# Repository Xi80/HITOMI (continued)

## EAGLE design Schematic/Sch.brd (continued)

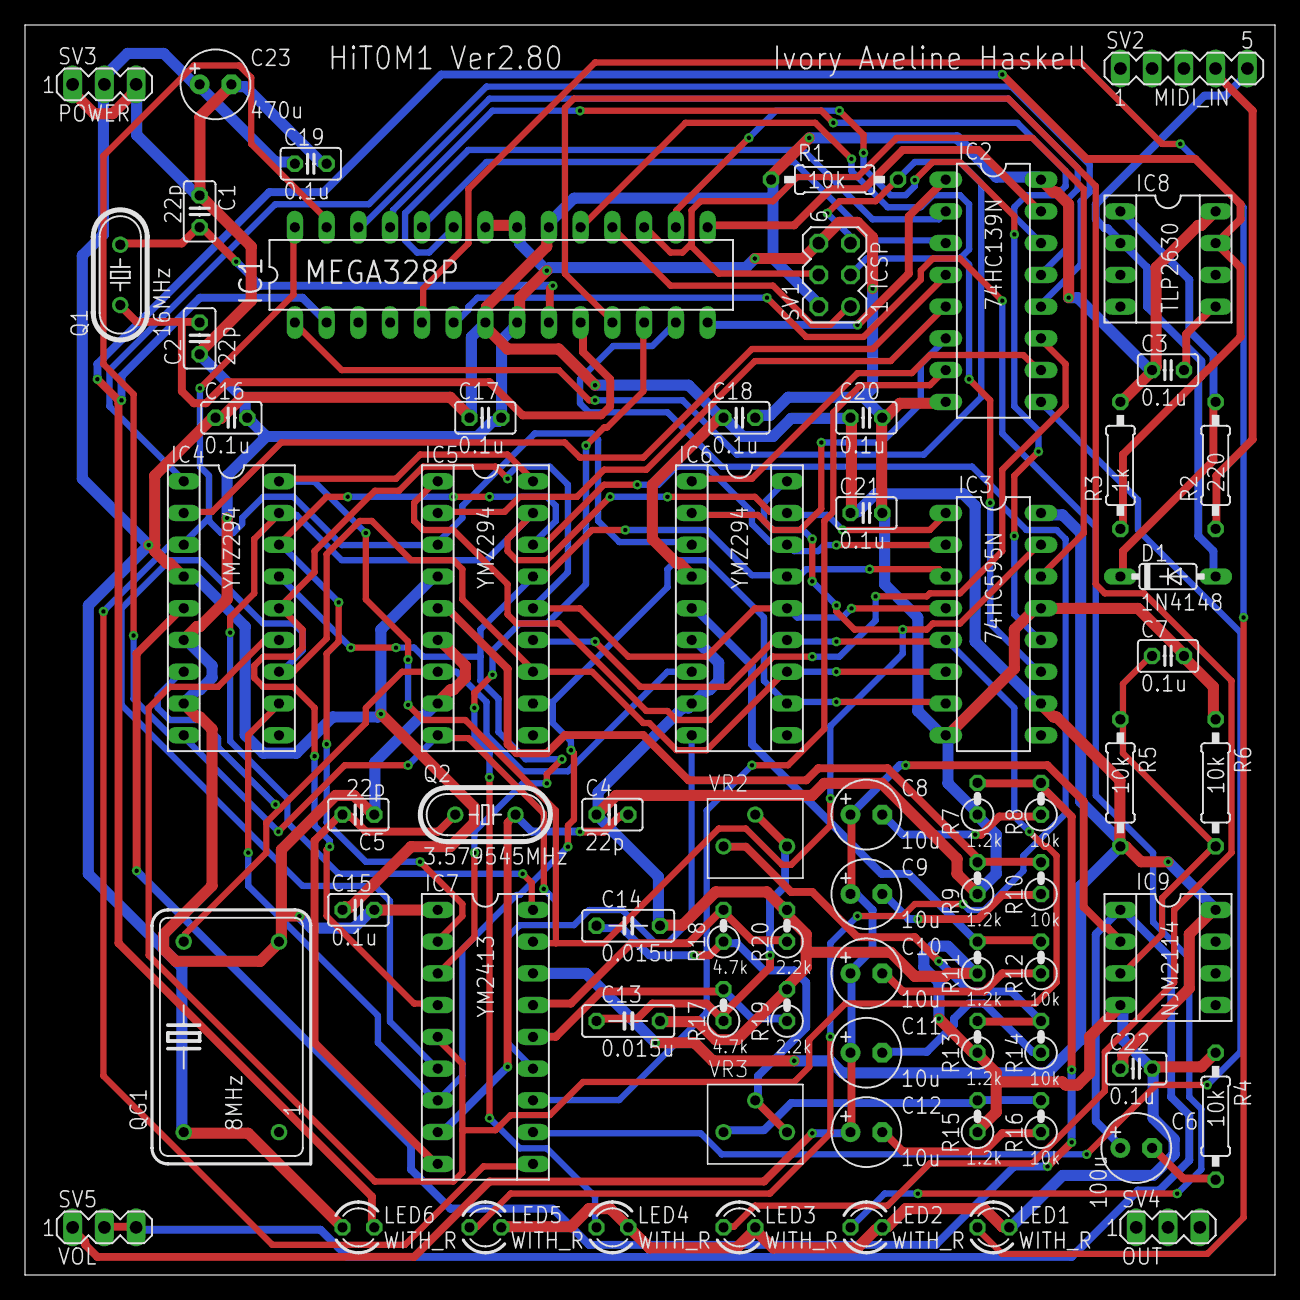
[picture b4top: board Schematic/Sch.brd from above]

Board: 2 copper layers, 100.0 x 100.0 mm, 69 parts (0 on the bottom side), 64 nets.

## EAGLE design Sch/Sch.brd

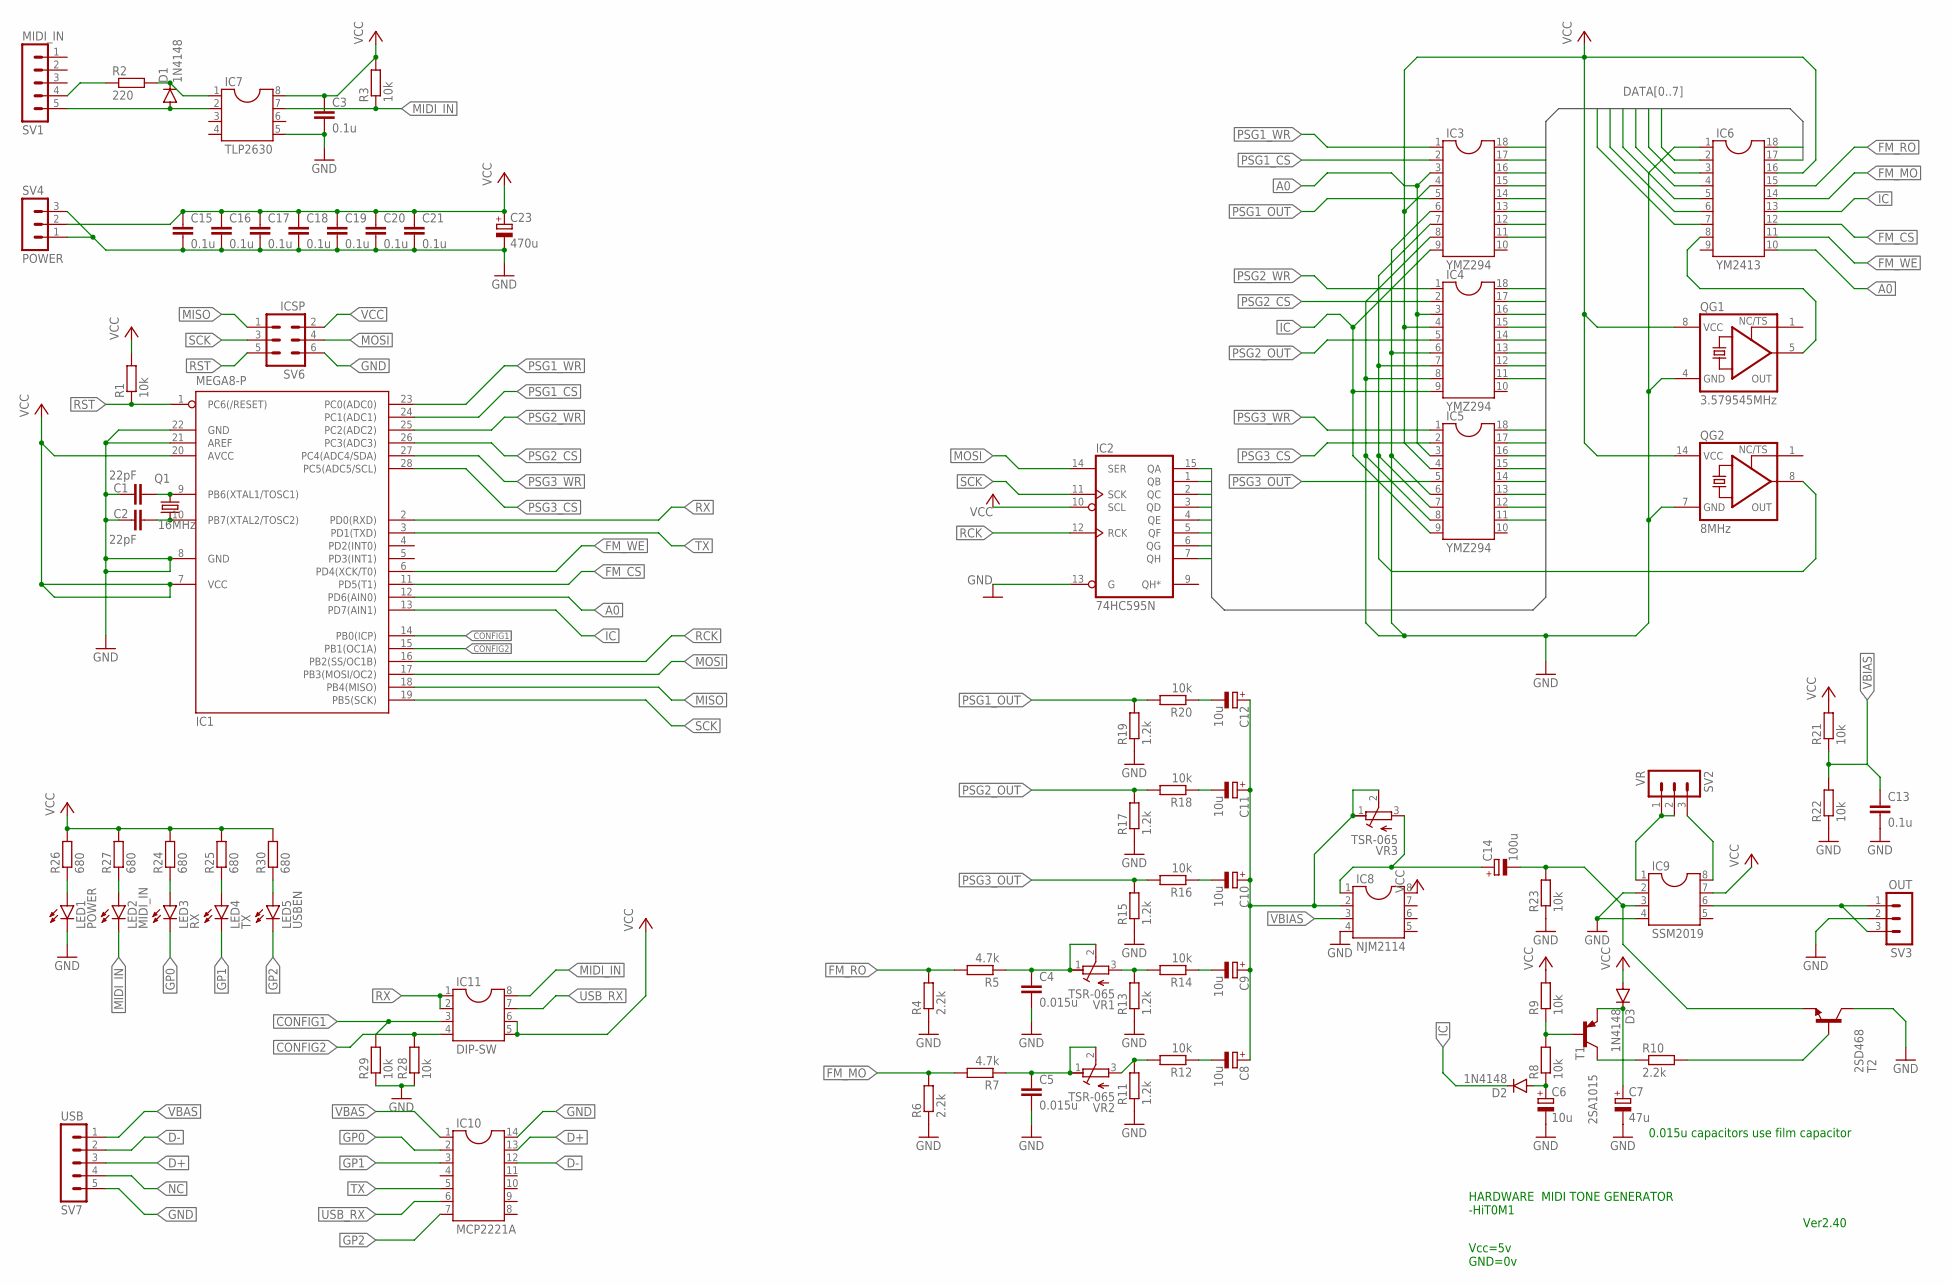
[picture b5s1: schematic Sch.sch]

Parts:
C1, C2: 22pF; C050-025X075
C3, C13, C15, C16, C17, C18, C19, C20, C21: 0.1u; C025-030X050
C4, C5: 0.015u; C050-025X075
C6, C8, C9, C10, C11, C12: 10u; E2,5-5
C7: 47u; E2,5-5
C14: 100u; E2,5-5
C23: 470u; E2,5-5
D1, D2, D3: 1N4148; DO35-7
IC1: MEGA8-P; DIL28-3
IC2: 74HC595N; DIL16
IC3, IC4, IC5: YMZ294; SOCKET-18
IC6: YM2413; SOCKET-18
IC7: TLP2630; SOCKET-08
IC8: NJM2114; SOCKET-08
IC9: SSM2019; SOCKET-08
IC10: MCP2221A; SOCKET-14
IC11: DIP-SW; SOCKET-08
LED1: POWER; LED3MM
LED2: MIDI_IN; LED3MM
LED3: RX; LED3MM
LED4: TX; LED3MM
LED5: USBEN; LED3MM
Q1: 16MHz; HC49/S
QG1: 3.579545MHz; DIL08S
QG2: 8MHz; DIL14S
R1, R3, R8, R9, R12, R14, R16, R18, R20, R21, R22, R23, R28, R29: 10k; 0207/2V
R2: 220; 0207/2V
R4, R6, R10: 2.2k; 0207/2V
R5, R7: 4.7k; 0207/2V
R11, R13, R15, R17, R19: 1.2k; 0207/2V
R24, R25, R26, R27, R30: 680; 0207/2V
SV1: MIDI_IN; MA05-1
SV2: VR; MA03-1
SV3: OUT; MA03-1
SV4: POWER; MA03-1
SV6: ICSP; MA03-2
SV7: USB; MA05-1
T1: 2SA1015; TO92
T2: 2SD468; TO92
VR1, VR2, VR3: TSR-065

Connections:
A0: IC1.12 (PD6(AIN0)), IC3.3, IC4.3, IC5.3, IC6.10
CONFIG1: IC1.14 (PB0(ICP)), IC11.3, R29.2
CONFIG2: IC1.15 (PB1(OC1A)), IC11.4, R28.2
D+: IC10.13, SV7.3
D-: IC10.12, SV7.2
DATA0: IC2.15 (QA), IC3.18, IC4.18, IC5.18, IC6.17
DATA1: IC2.1 (QB), IC3.17, IC4.17, IC5.17, IC6.18
DATA2: IC2.2 (QC), IC3.16, IC4.16, IC5.16, IC6.2
DATA3: IC2.3 (QD), IC3.15, IC4.15, IC5.15, IC6.3
DATA4: IC2.4 (QE), IC3.14, IC4.14, IC5.14, IC6.4
DATA5: IC2.5 (QF), IC3.13, IC4.13, IC5.13, IC6.5
DATA6: IC2.6 (QG), IC3.12, IC4.12, IC5.12, IC6.6
DATA7: IC2.7 (QH), IC3.11, IC4.11, IC5.11, IC6.7
FM_CS: IC1.11 (PD5(T1)), IC6.12
FM_MO: IC6.14, R6.2, R7.2
FM_RO: IC6.15, R4.2, R5.2
FM_WE: IC1.6 (PD4(XCK/T0)), IC6.11
GND: C1.2, C2.2, C3.2, C4.2, C5.2, C6.-, C7.-, C13.2, C15.2, C16.2, C17.2, C18.2, C19.2, C20.2, C21.2, C23.-, IC1.8 (GND), IC1.21 (AREF), IC1.22 (GND), IC2.8 (GND), IC2.13 (G), IC3.6, IC3.8, IC4.6, IC4.8, IC5.6, IC5.8, IC6.1, IC7.5, IC8.4, IC9.2, IC9.4, IC10.14, LED1.K (C), QG1.4 (GND), QG2.7 (GND), R4.1, R6.1, R11.1, R13.1, R15.1, R17.1, R19.1, R22.1, R23.1, R28.1, R29.1, SV3.2, SV4.1, SV4.3, SV6.6, SV7.5, T2.3 (C)
GP0: IC10.2, LED3.K (C)
GP1: IC10.3, LED4.K (C)
GP2: IC10.7, LED5.K (C)
IC: D2.C, IC1.13 (PD7(AIN1)), IC3.9, IC4.9, IC5.9, IC6.13
MIDI_IN: IC7.7, IC11.8, LED2.K (C), R3.1
MISO: IC1.18 (PB4(MISO)), SV6.1
MOSI: IC1.17 (PB3(MOSI/OC2)), IC2.14 (SER), SV6.4
unnamed: R2.1, SV1.4
unnamed: D1.A, IC7.2, SV1.5
unnamed: C1.1, IC1.9 (PB6(XTAL1/TOSC1)), Q1.2
unnamed: C2.1, IC1.10 (PB7(XTAL2/TOSC2)), Q1.1
unnamed: D1.C, IC7.1, R2.2
unnamed: IC3.7, IC4.7, IC5.7, QG2.8 (OUT)
unnamed: C6.+, D2.A, R8.1
unnamed: C4.1, R5.1, VR1.1 (A), VR1.2 (S)
unnamed: IC6.8, QG1.5 (OUT)
unnamed: C8.+, C9.+, C10.+, C11.+, C12.+, IC8.2, VR3.1 (A), VR3.2 (S)
unnamed: C5.1, R7.1, VR2.1 (A), VR2.2 (S)
unnamed: LED3.A, R24.1
unnamed: R8.2, R9.1, T1.2 (B)
unnamed: C7.+, D3.C, T1.1 (E)
unnamed: R10.1, T1.3 (C)
unnamed: R10.2, T2.2 (B)
unnamed: C14.-, IC9.3, R23.2, T2.1 (E)
unnamed: R11.2, R12.2, VR2.3 (E)
unnamed: C8.-, R12.1
unnamed: R13.2, R14.2, VR1.3 (E)
unnamed: C9.-, R14.1
unnamed: LED4.A, R25.1
unnamed: C10.-, R16.1
unnamed: LED5.A, R30.1
unnamed: C11.-, R18.1
unnamed: LED1.A, R26.1
unnamed: C12.-, R20.1
unnamed: C14.+, IC8.1, VR3.3 (E)
unnamed: IC9.1, SV2.1, SV2.2
unnamed: IC9.8, SV2.3
unnamed: LED2.A, R27.1
unnamed: IC9.6, SV3.1, SV3.3
NC: SV7.4
PSG1_CS: IC1.24 (PC1(ADC1)), IC3.2
PSG1_OUT: IC3.5, R19.2, R20.2
PSG1_WR: IC1.23 (PC0(ADC0)), IC3.1
PSG2_CS: IC1.26 (PC3(ADC3)), IC4.2
PSG2_OUT: IC4.5, R17.2, R18.2
PSG2_WR: IC1.25 (PC2(ADC2)), IC4.1
PSG3_CS: IC1.28 (PC5(ADC5/SCL)), IC5.2
PSG3_OUT: IC5.5, R15.2, R16.2
PSG3_WR: IC1.27 (PC4(ADC4/SDA)), IC5.1
RCK: IC1.16 (PB2(SS/OC1B)), IC2.12 (RCK)
RST: IC1.1 (PC6(/RESET)), R1.1, SV6.5
RX: IC1.2 (PD0(RXD)), IC11.1, IC11.2
SCK: IC1.19 (PB5(SCK)), IC2.11 (SCK), SV6.3
TX: IC1.3 (PD1(TXD)), IC10.5
USB_RX: IC10.6, IC11.7
VBAS: IC10.1, SV7.1
VBIAS: C13.1, IC8.3, R21.1, R22.2
VCC: C3.1, C15.1, C16.1, C17.1, C18.1, C19.1, C20.1, C21.1, C23.+, D3.A, IC1.7 (VCC), IC1.20 (AVCC), IC2.10 (SCL), IC2.16 (VCC), IC3.4, IC4.4, IC5.4, IC6.16, IC7.8, IC8.8, IC9.7, IC11.5, IC11.6, QG1.8 (VCC), QG2.14 (VCC), R1.2, R3.2, R9.2, R21.2, R24.2, R25.2, R26.2, R27.2, R30.2, SV4.2, SV6.2

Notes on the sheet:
HARDWARE MIDI TONE GENERATOR -HiT0M1
Ver2.40
Vcc=5v GND=0v
0.015u capacitors use film capacitor

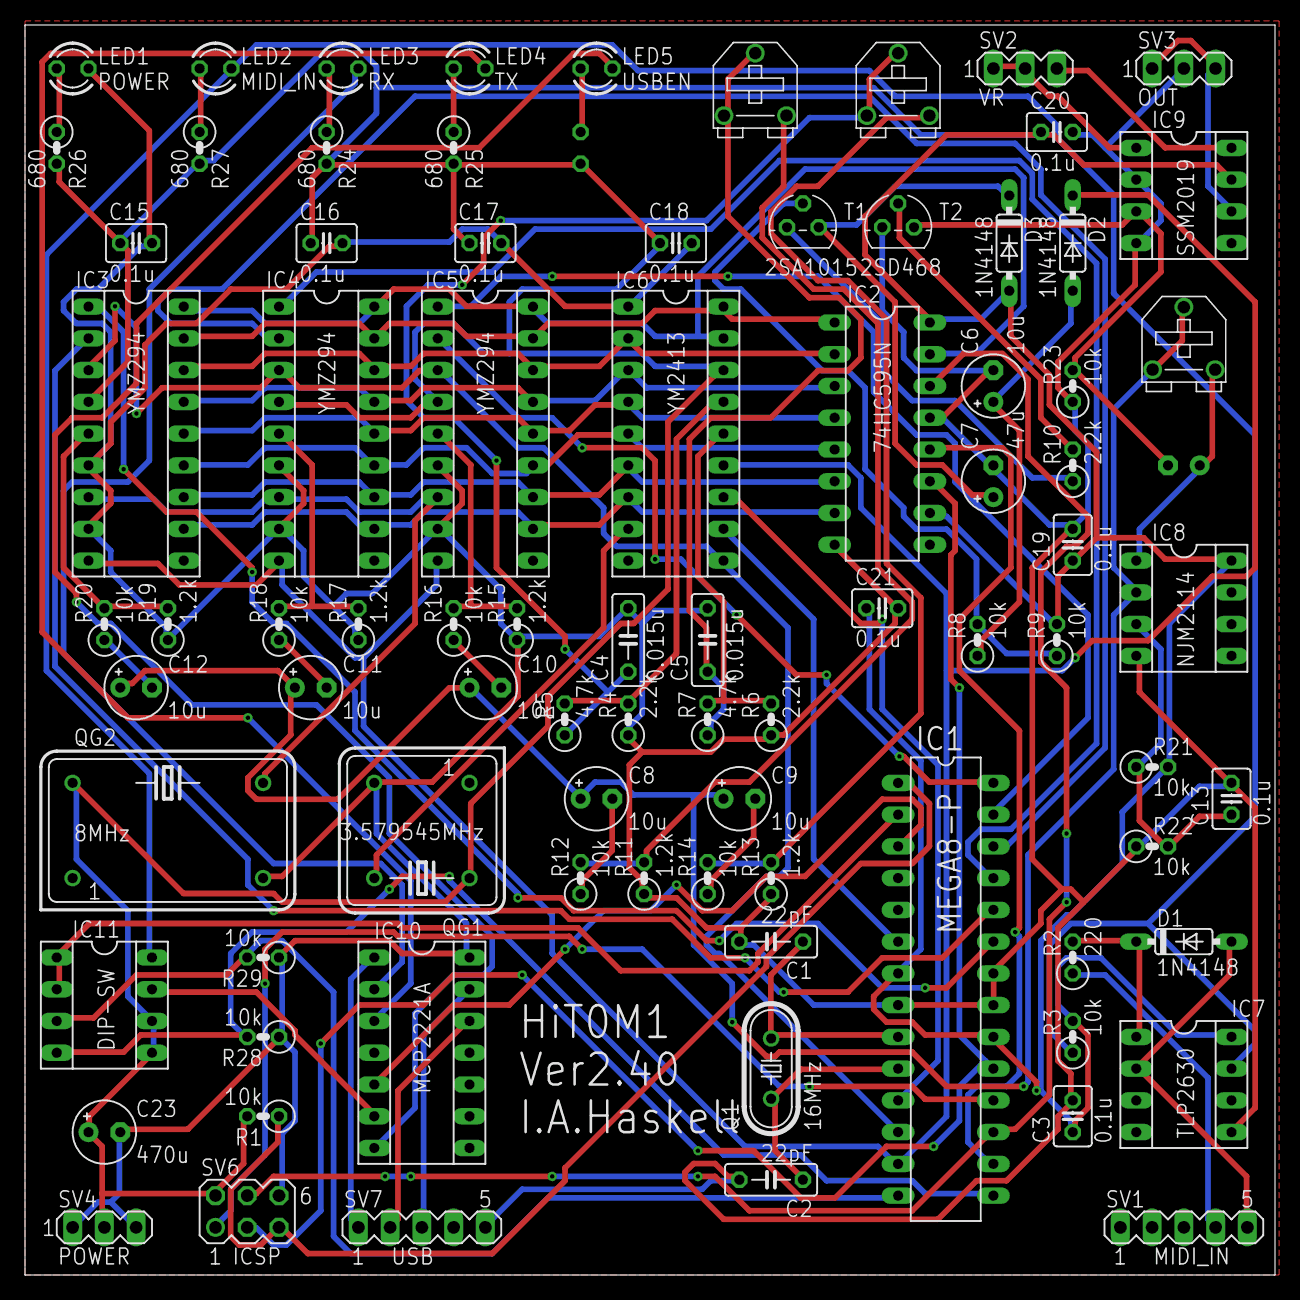
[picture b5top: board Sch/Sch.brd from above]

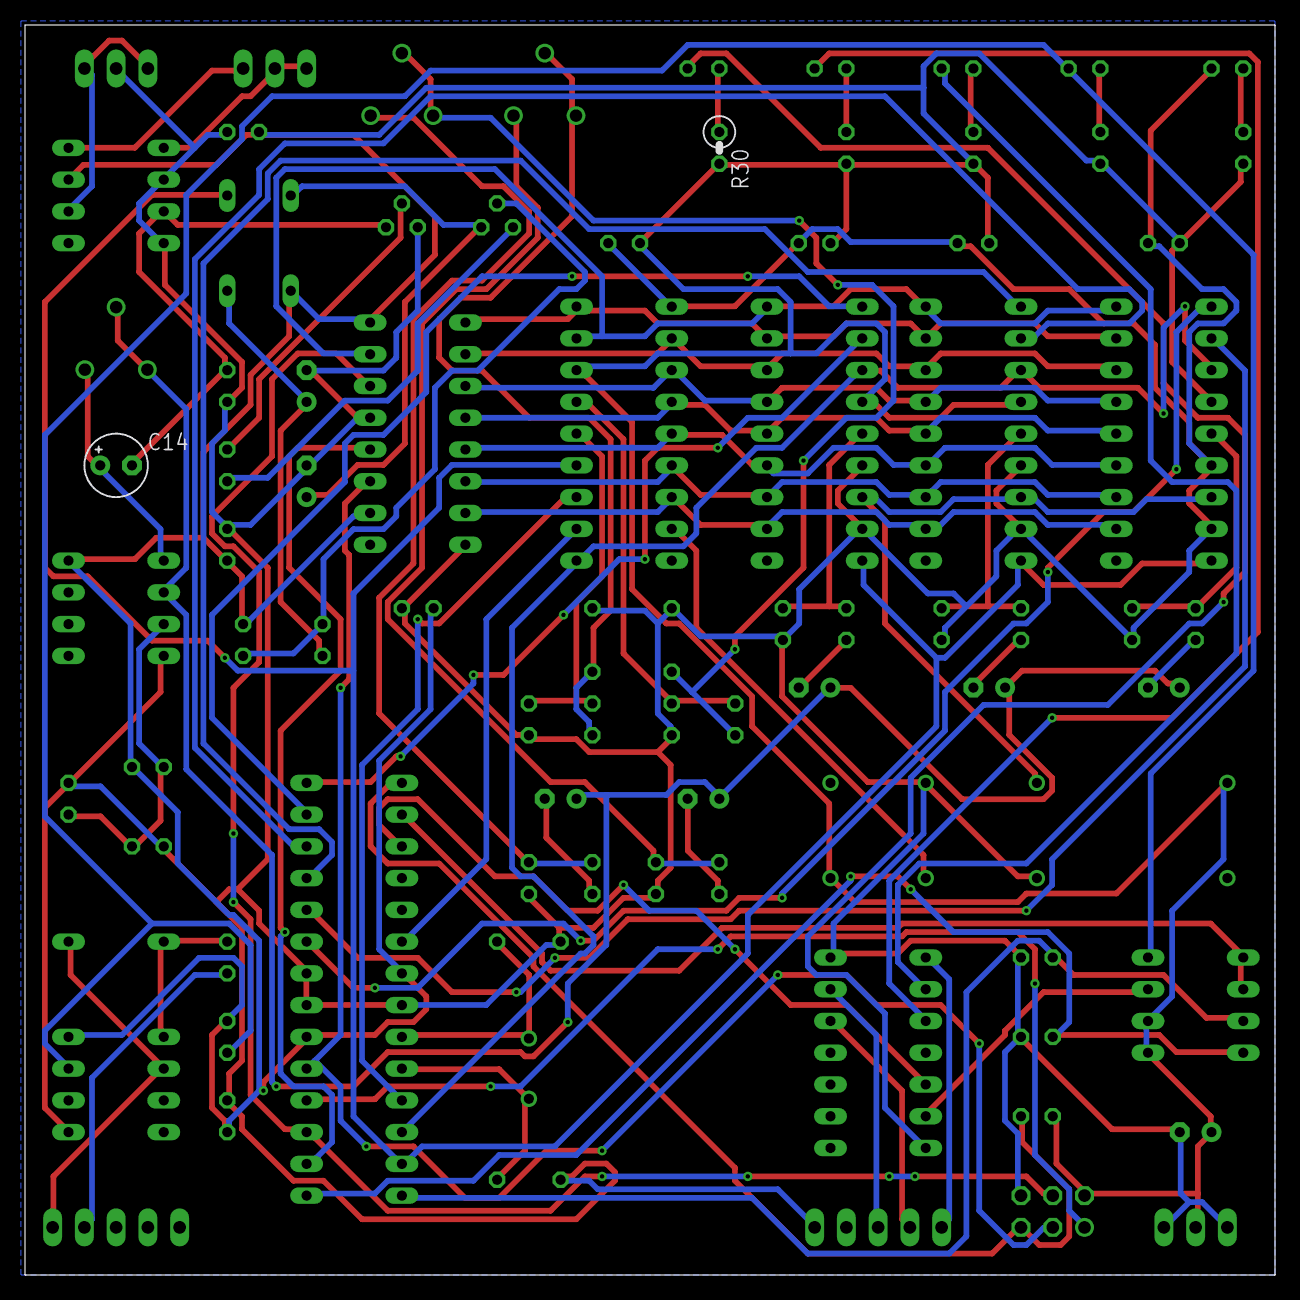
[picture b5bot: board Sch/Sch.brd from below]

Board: 2 copper layers, 100.0 x 100.0 mm, 85 parts (2 on the bottom side), 75 nets.

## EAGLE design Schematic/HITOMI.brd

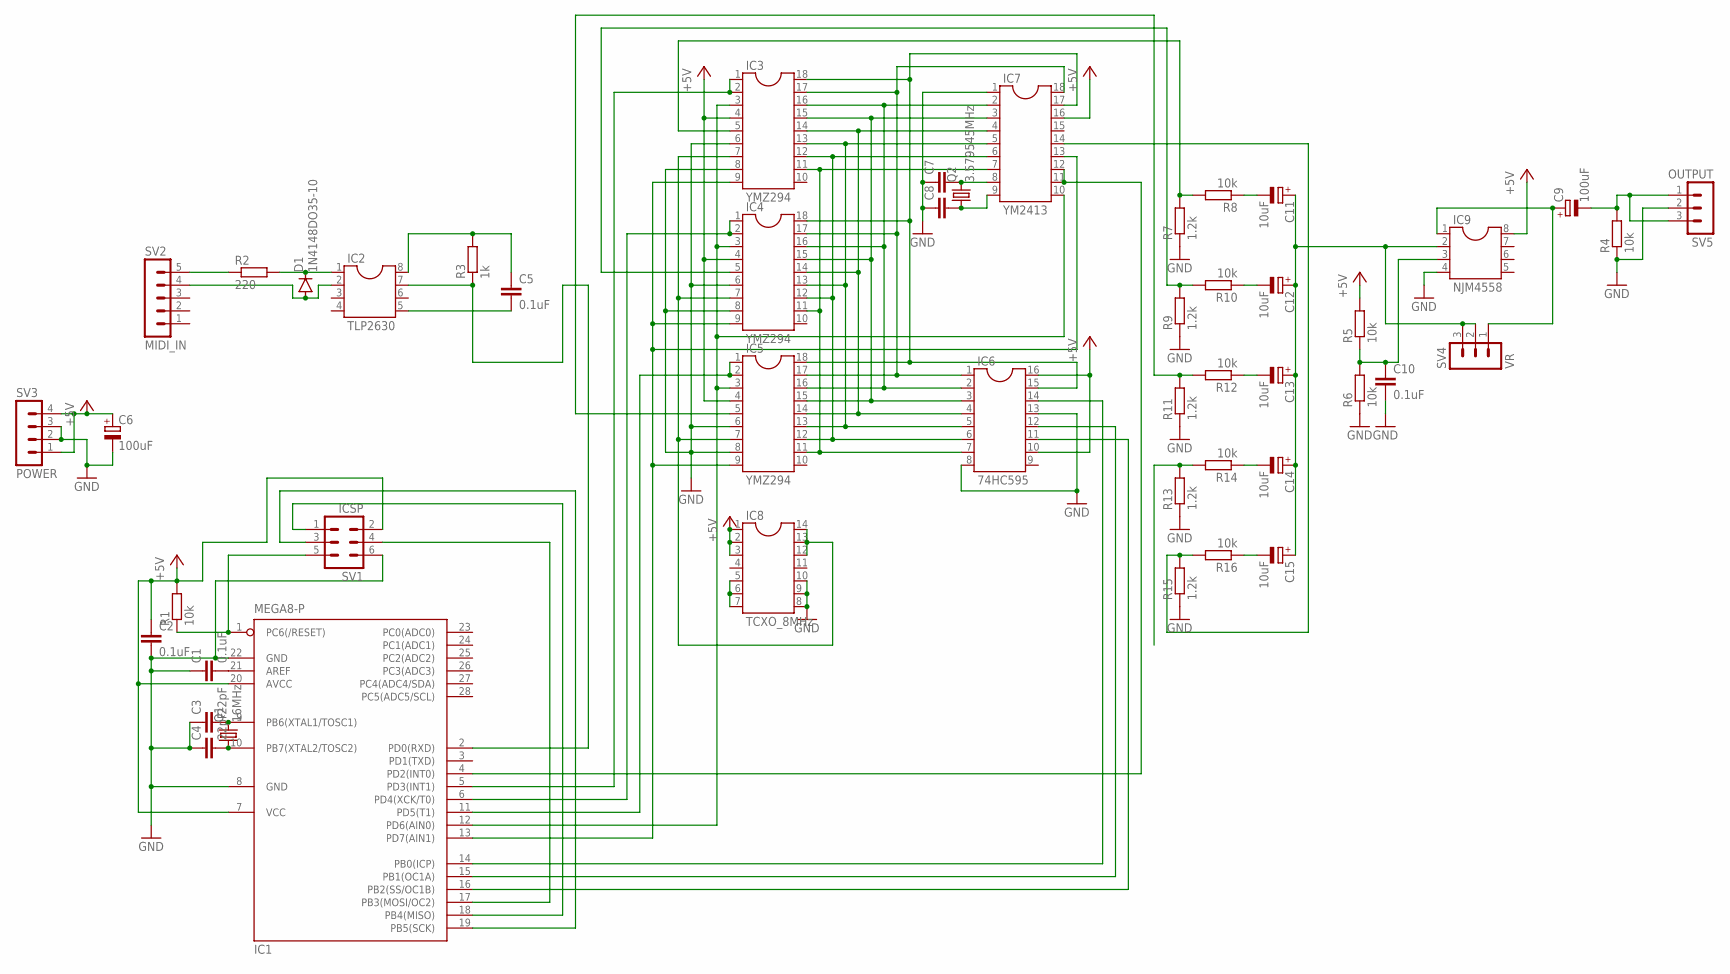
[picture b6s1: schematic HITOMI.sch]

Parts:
C1, C2, C5, C10: 0.1uF; C050-025X075
C3, C4: 22pF; C050-025X075
C6, C9: 100uF; E2,5-7
C7, C8: C-EU050-025X075; C050-025X075
C11, C12, C13, C14, C15: 10uF; E2,5-7
D1: 1N4148DO35-10; DO35-10
IC1: MEGA8-P; DIL28-3
IC2: TLP2630; DIL08
IC3, IC4, IC5: YMZ294; SOCKET-18
IC6: 74HC595; SOCKET-16
IC7: YM2413; SOCKET-18
IC8: TCXO_8MHz; DIL14
IC9: NJM4558; DIL08
Q1: 16MHz; HC49/S
Q2: 3.579545MHz; HC49/S
R1, R4, R5, R6, R8, R10, R12, R14, R16: 10k; 0207/10
R2: 220; 0207/10
R3: 1k; 0207/10
R7, R9, R11, R13, R15: 1.2k; 0207/10
SV1: ICSP; MA03-2
SV2: MIDI_IN; MA05-1
SV3: POWER; MA04-1
SV4: VR; MA03-1
SV5: OUTPUT; MA03-1

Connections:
+5V: C2.1, C6.+, IC1.7 (VCC), IC1.20 (AVCC), IC3.4, IC4.4, IC5.4, IC6.10, IC6.16, IC7.16, IC8.1, IC8.2, IC8.3, IC9.8, R1.2, R5.2, SV1.2, SV3.1, SV3.4
GND: C1.1, C2.2, C3.1, C4.1, C6.-, C7.1, C8.1, C10.2, IC1.8 (GND), IC1.22 (GND), IC3.6, IC3.8, IC4.6, IC4.8, IC5.6, IC5.8, IC6.8, IC6.13, IC7.1, IC8.8, IC8.9, IC8.10, IC9.4, R4.1, R6.1, R7.1, R9.1, R11.1, R13.1, R15.1, SV1.6, SV3.2, SV3.3, SV5.2
unnamed: IC1.1 (PC6(/RESET)), R1.1, SV1.5
unnamed: IC1.17 (PB3(MOSI/OC2)), SV1.4
unnamed: IC1.18 (PB4(MISO)), SV1.1
unnamed: C1.2, IC1.21 (AREF)
unnamed: C3.2, IC1.9 (PB6(XTAL1/TOSC1)), Q1.2
unnamed: C4.2, IC1.10 (PB7(XTAL2/TOSC2)), Q1.1
unnamed: IC1.19 (PB5(SCK)), SV1.3
unnamed: IC3.18, IC4.18, IC5.18, IC6.15, IC7.17
unnamed: D1.A, IC2.2, SV2.4
unnamed: R2.1, SV2.5
unnamed: D1.C, IC2.1, R2.2
unnamed: C5.1, IC2.8, R3.2
unnamed: C5.2, IC2.5
unnamed: IC1.5 (PD3(INT1)), IC3.1, IC3.2
unnamed: IC3.11, IC4.11, IC5.11, IC6.7, IC7.7
unnamed: IC3.12, IC4.12, IC5.12, IC6.6, IC7.6
unnamed: IC3.13, IC4.13, IC5.13, IC6.5, IC7.5
unnamed: IC3.14, IC4.14, IC5.14, IC6.4, IC7.4
unnamed: IC3.15, IC4.15, IC5.15, IC6.3, IC7.3
unnamed: IC3.16, IC4.16, IC5.16, IC6.2, IC7.2
unnamed: IC3.17, IC4.17, IC5.17, IC6.1, IC7.18
unnamed: IC1.6 (PD4(XCK/T0)), IC4.1, IC4.2
unnamed: IC1.11 (PD5(T1)), IC5.1, IC5.2
unnamed: IC1.12 (PD6(AIN0)), IC3.3, IC4.3, IC5.3, IC7.10
unnamed: C11.+, C12.+, C13.+, C14.+, C15.+, IC9.2, SV4.2, SV4.3
unnamed: IC1.4 (PD2(INT0)), IC7.11, IC7.12
unnamed: IC3.7, IC4.7, IC5.7, IC8.12, IC8.13, IC8.14
unnamed: IC8.5, IC8.6, IC8.7
unnamed: IC1.13 (PD7(AIN1)), IC3.9, IC4.9, IC5.9, IC7.13
unnamed: C9.+, IC9.1, SV4.1
unnamed: C7.2, IC7.8, Q2.2
unnamed: C8.2, IC7.9, Q2.1
unnamed: IC1.14 (PB0(ICP)), IC6.14
unnamed: IC1.15 (PB1(OC1A)), IC6.12
unnamed: IC1.16 (PB2(SS/OC1B)), IC6.11
unnamed: C10.1, IC9.3, R5.1, R6.2
unnamed: C9.-, R4.2, SV5.1, SV5.3
unnamed: IC3.5, R7.2, R8.2
unnamed: C11.-, R8.1
unnamed: IC4.5, R9.2, R10.2
unnamed: C12.-, R10.1
unnamed: IC5.5, R11.2, R12.2
unnamed: C13.-, R12.1
unnamed: R13.2, R14.2
unnamed: C14.-, R14.1
unnamed: IC7.14, R15.2, R16.2
unnamed: C15.-, R16.1
unnamed: IC1.2 (PD0(RXD)), IC2.7, R3.1

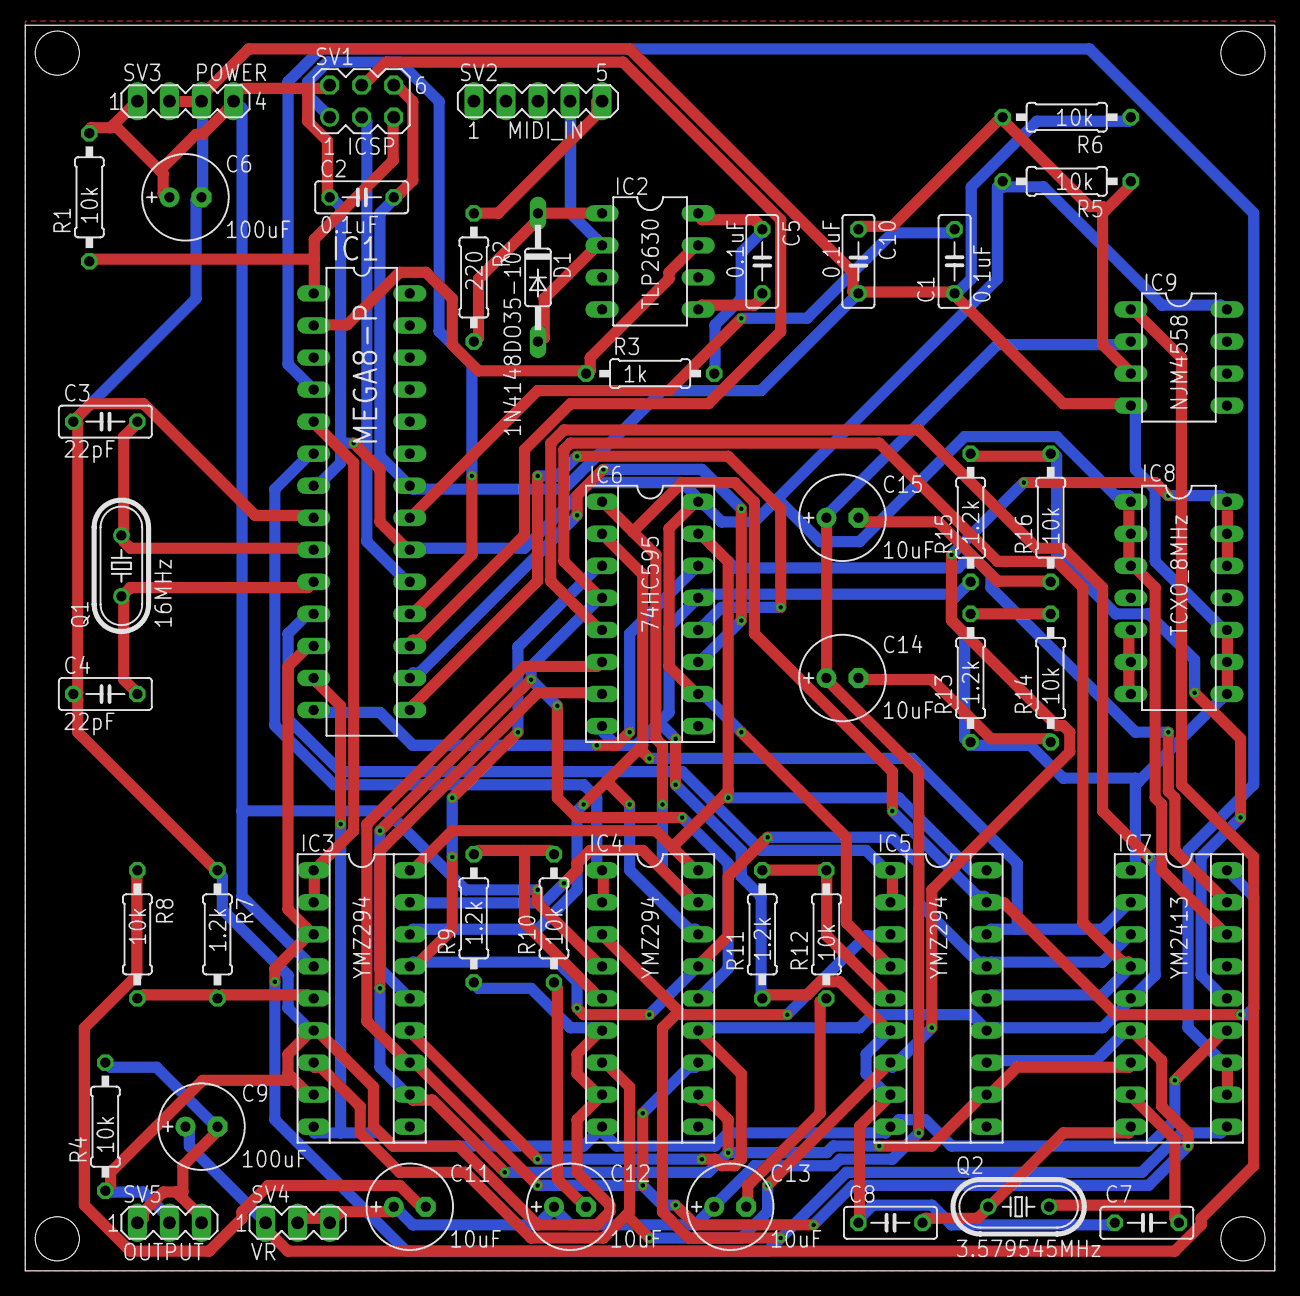
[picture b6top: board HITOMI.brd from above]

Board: 2 copper layers, 99.0 x 98.7 mm, 48 parts (0 on the bottom side), 50 nets.

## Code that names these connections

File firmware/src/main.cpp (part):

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//ピン名の定義

// 74HC595
#define SRCLK       (PB5)
#define RCLK        (PB2)
#define SER         (PB3)

// 74HC139
#define CS_A        (PC0)
#define CS_B        (PC1)
#define CS_E        (PB0)

#define WR_A        (PC2)
#define WR_B        (PC3)
#define WR_E        (PB1)

// Tone Generator
#define IC_PIN      (PC4)
#define A0_PIN      (PC5)

// Status LEDs
#define GP_LED1     (PD3)
#define GP_LED2     (PD4)
#define GP_LED3     (PD5)
#define GP_LED4     (PD6)
#define GP_LED5     (PD7)
//-----------------------------------

//-----------------------------------
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
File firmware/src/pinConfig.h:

/*
 *
 * HiT0M1 Pin Config File
 *  
*/
#ifndef PINCONFIG
#define PINCONFIG

// 74HC595
#define SRCLK       (13)
#define RCLK        (10)
#define SER         (11)

// 74HC139
#define CS_A        (14)
#define CS_B        (15)
#define CS_E        (8)

#define WR_A        (16)
#define WR_B        (17)
#define WR_E        (9)
// Tone Generator
#define IC_PIN      (18)
#define A0_PIN      (19)

// Status LEDs
#define PSG1_LED    (3)    
#define PSG2_LED    (4)
#define PSG3_LED    (5)
#define FMR_LED     (6)
#define FMM_LED     (7)

#endif

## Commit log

2020-04-03 change-readme
    readmeをちょっと書いた
2020-04-07 Whole Changes
2020-04-07 Add Component
2020-04-07 Add Logo
2020-04-08 Change
2020-04-08 Remove Schematic
2020-04-08 Remove
2020-04-11 Update Files
2020-04-11 Fix file names
2020-04-11 Firmware Update
2020-04-12 Firmware Update2
2020-04-12 Add NoteON(PSG)
2020-04-12 Add NoteOFF
2020-04-12 Wrote All functions
2020-04-12 Some Fix
2020-04-12 Add description
2020-04-14 WIP_Nucleo
2020-04-14 Wrote all of the firmware
2020-04-14 License
2020-04-15 Update
    Removed Old Firmware And Add Description
2020-04-15 Whole Changes
    Update Readme.md and Added gerber files,change pictures of the circuit
2020-04-15 temp
2020-04-15 fix images
2020-04-15 Update
    WHOLE CHANGE
2020-04-15 Fix pin configs
2020-04-16 Fix board
2020-04-16 Update Schematics
2020-04-16 Fix Schematics
2020-04-17 GOOD NIGHT
    Good night,Hitomi
